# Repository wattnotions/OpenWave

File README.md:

# OpenWave
Open Source Ocean Wave Sensor

For latest updates on where this project is at, visit http://www.wattnotions.com/category/openwave/

Copyright 2019

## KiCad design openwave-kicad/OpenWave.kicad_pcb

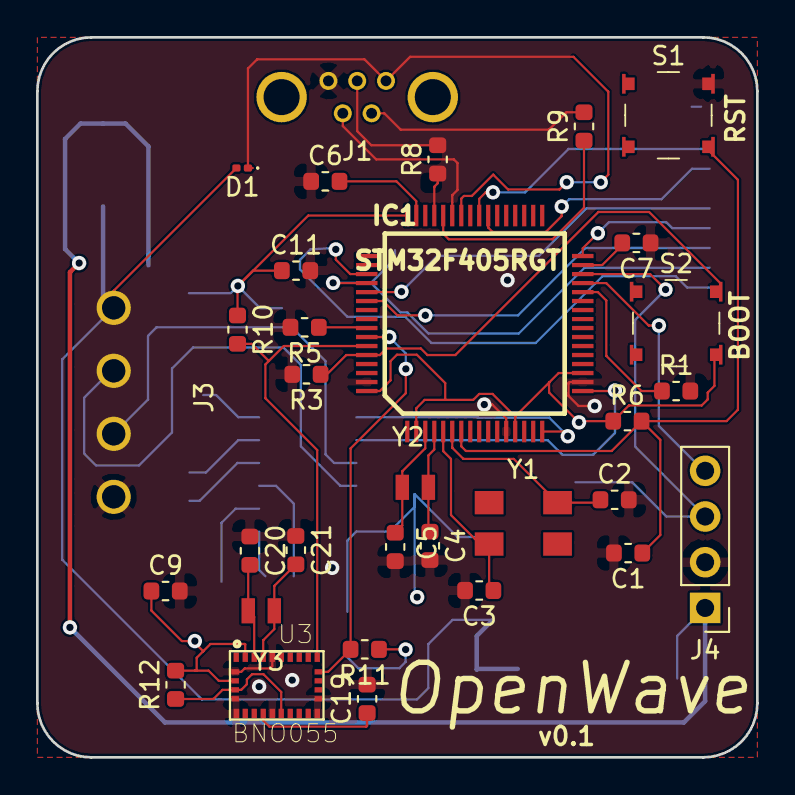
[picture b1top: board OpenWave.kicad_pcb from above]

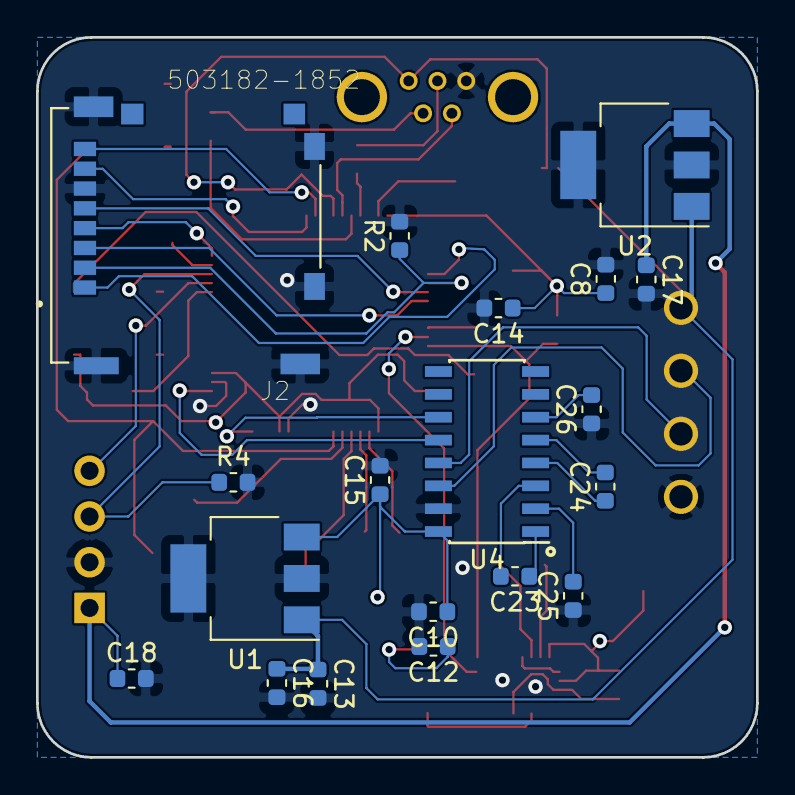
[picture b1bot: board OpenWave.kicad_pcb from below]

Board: 4 copper layers, 40.0 x 40.0 mm, 51 parts (19 on the bottom side), 44 nets.

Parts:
C1, C8, C9, C10, C11, C15, C18: 100n; C_0603_1608Metric
C2, C3, C4, C5: 12p; C_0603_1608Metric
C6, C7: 2u2; C_0603_1608Metric
C12: 4u7; C_0603_1608Metric
C13, C14, C16, C17: 1u; C_0603_1608Metric
C19: 22pf; C_0603_1608Metric
C20, C21: 12pf; C_0603_1608Metric
C23, C24, C25, C26: 0.1uF; C_0603_1608Metric
D1: D_Schottky; D_0201_0603Metric
IC1: STM32F405RGT; LQFP64
J1: USB_OTG; wurth_usb_connector
J2: 503182-1852; MOLEX_503182-1852
J3: Screw_Terminal_01x04; 4-WAY-PCB_SOCKET
J4: Conn_01x04_Female; PinHeader_1x04_P2.54mm_Vertical
R1: 1k; R_0603_1608Metric
R2: 10M; R_0603_1608Metric
R3, R4, R5: 100k; R_0603_1608Metric
R6: 10K; R_0603_1608Metric
R8, R9: 15R; R_0603_1608Metric
R10, R11, R12: 10k; R_0603_1608Metric
S1, S2: TL3315NF160Q; Switch_Tactile_SMD_4.5x4.5mm_TL3315NF160Q
U1: MIC5239-3.3YS; SOT-223-3_TabPin2
U2: MIC5209-4.2; SOT-223-3_TabPin2
U3: BNO055; LGA28R50P4X10_380X520X100
U4: MAX3232; SOIC-16_3.9x9.9mm_P1.27mm
Y1: 8MHz; QC5CA8_8mhz_oscillator
Y2: 32.768KHz; ABS06-32.768KHZ_smd_crystal
Y3: Crystal; ABS06-32.768KHZ_smd_crystal

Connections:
+3V3: C8.1, C9.1, C10.1, C11.1, C12.1, C14.1, C15.1, IC1.2, IC1.13, IC1.19, IC1.32, IC1.48, IC1.64, J2.4, R6.1, R10.1, R11.1, R12.2, S2.4, U1.3, U3.3, U3.28, U4.16
+5V: D1.1, IC1.42, J1.1
+12V: C13.1, C16.1, D1.2, J3.4, U1.1, U2.1
/4.2V: C17.1, C18.1, J4.1, U2.3
/BNO055/XIN32: C20.2, U3.27, Y3.1
/BNO055/XOUT32: C21.2, U3.26, Y3.2
/BOOT0: IC1.60, R3.1, S2.2
/FS_DM: IC1.44, R9.1
/FS_DP: IC1.45, R8.1
/FS_USB_ID: IC1.43, J1.4
/I2C1-SCK: IC1.58, R11.2, U3.19
/I2C1-SDA: IC1.59, R10.2, U3.20
/IO_PA2: IC1.16, U4.11
/IO_PA3: IC1.17, U4.12
/IO_PB2: IC1.28, R1.1
/IO_PB10: IC1.29, J4.4
/IO_PB11: IC1.30, J4.3, R4.1
/MMA_AVDD: IC1.57, R5.1
/N$1: C6.2, IC1.47
/N$2: C7.2, IC1.31
/N$5: C5.1, IC1.3, Y2.2
/N$6: C4.1, IC1.4, Y2.1
/N$9: C2.1, IC1.6, Y1.1
/N$10: C3.1, IC1.5, Y1.2
/NRST: C1.1, IC1.7, R6.2, S1.4
/RS232_RX: J3.2, U4.13
/RS232_TX: J3.3, U4.14
/SDIO_CK: IC1.53, J2.5
/SDIO_CMD: IC1.54, J2.3
/SDIO_D0: IC1.39, J2.7
/SDIO_D1: IC1.40, J2.8
/SDIO_D2: IC1.51, J2.1
/SDIO_D3: IC1.52, J2.2, R2.1
GND: C1.2, C2.2, C3.2, C4.2, C5.2, C6.1, C7.1, C8.2, C9.2, C10.2, C11.2, C12.2, C13.2, C14.2, C15.2, C16.2, C17.2, C18.2, C19.2, C20.1, C21.1, C25.1, C26.1, IC1.12, IC1.18, IC1.63, J1.5, J2.6, J2.P1, J2.P2, J2.P3, J2.P4, J2.P5, J3.1, J4.2, R1.2, R2.2, R3.2, R4.2, R5.2, S1.2, U1.2, U2.2, U3.2, U3.5, U3.6, U3.10, U3.15, U3.16, U3.25, U4.15
unnamed: C19.1, U3.9
unnamed: C23.1, U4.1
unnamed: C23.2, U4.3
unnamed: C24.1, U4.4
unnamed: C24.2, U4.5
unnamed: C25.2, U4.2
unnamed: C26.2, U4.6
unnamed: J1.2, R9.2
unnamed: J1.3, R8.2
unnamed: R12.1, U3.4, U3.11

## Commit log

2019-02-26 changed directory name of test data file
2019-02-26 added example dataset
2019-02-26 added list chunk function
2019-02-28 part way through chunk_integration
2019-02-28 chunk_integrate function first revision completed and working
2019-02-28 removed unneeded list copy
2019-02-28 added plot detrended velocity func
2019-02-28 added find_peaks and integrated into chunk_integrate
2019-02-28 added average max displacement calculation
2019-03-03 added example plot function
2019-03-03 cleaned up end debug related lines
2019-03-22 removed debug info - added example plot 2
2019-03-22 added zero crossing test to chunk integrate
2019-03-22 added comments to chunk_integrate()
2019-04-04 added remove dc offset, made chunk integrate better
2019-04-05 made chunk graph more accurate
2019-04-05 added sine wave test + triple subplot
2019-04-05 tidied up code, partioned into functions, removed debug code
2019-04-05 changed example csv file
2019-04-05 added time_to_get_chunky function
2019-04-05 renamed to openwave.py
2019-04-05 main script with fancy new name
2019-04-05 removed example plot functions
2019-04-06 moved to python-scripts directory
2019-04-06 new subfolder for python scripts
2019-04-06 added kicad project as subfolder
2019-04-06 cleaned up more debug code, left in working state
2019-04-06 added mic5239 datasheet
2019-04-06 added mic5239 v reg
2019-04-06 added bno055 lib and footprint
2019-04-06 added sheet for bno055
2019-04-06 added max3232 sheet
2019-04-06 added 4.2v reg datasheet
2019-04-06 added bluetooth header, 4.2v reg
2019-04-06 added max232 datasheet
2019-04-06 finished max232 schematic
2019-04-07 added bno055 datasheet
2019-04-07 finished bno055 schematic
2019-04-08 added sd card connector footprint
2019-04-08 added digikey lib
2019-04-08 added pyboard lib
2019-04-08 linked all footprints to symbols, ready for routing
2019-04-08 fixed unconnected nets, routing 15% done
2019-04-09 routing ...51 connections left
2019-04-09 routing finished
2019-04-09 replaced incorrect usb connector
2019-04-09 added openwave to front silk
2019-04-09 added pin 1 marker to max3232
2019-04-09 made screw terminal pads thicker
2019-04-09 made screw terminal pads even thicker
2019-04-10 working on zero crossing displacement calculations
2019-04-10 removed debug print from threshpeaks
2019-04-10 fixed chunk integrate bug caused by type
2019-04-10 added comments to time to get chunky
2019-04-10 removed old example data file
2019-04-10 updated to reflect new example data files
2019-04-10 new test data files
2019-04-10 added comments explaining functions
2019-04-11 increased zero crossing interval
2019-04-12 added peak detect and zero crossing displacement functions
2019-04-12 added percentage error calculatioN
2019-04-12 added make error measurements function
2019-04-12 added pretty table error output
2019-04-12 added arguments to script, error, zero and peak
2019-04-24 added lowpass bode plot, made zero and peak func smarter with plot=yes/no
2019-05-31 added readme
2019-11-25 moved test_data to root dir
2019-11-25 Created script1.m
2019-11-26 added .asv to gitignore
2019-11-26 add fft_example for matlab website
2019-11-26 got fft plot working with correct freq scale
2019-11-26 added imu displacement info doc
2019-11-28 got freq domain accel2disp example from stackoverflow
2019-12-09 added paper on bares wave sensor
2019-12-09 added paper on FFT-DDI method
2019-12-12 added oceanography book
2019-12-12 added data from ocean energy ireland
2019-12-12 moved arm data to seperate folder
2019-12-12 moved files to seperate folder
2019-12-13 added *.djvu to gitignore
2019-12-13 restructed related_docs folder
2019-12-13 modified dir structure
2019-12-16 added sine gen function
2019-12-16 gave more descriptive name
2019-12-17 added randraw lib for rayleigh gen
2019-12-17 added test plot script for rayleigh dist
2019-12-17 added stoptime argument
2019-12-17 started work on sig wave gen
2019-12-18 got vector append to array working
2019-12-18 added sample rate argument
2019-12-18 replaced hardcoded values with variables
2019-12-18 changed more hardcoded to variable
2019-12-18 add all waves together and plot done
2019-12-19 added formatted value printing
2019-12-19 renamed to oceanWaveSim
2019-12-19 made script into a function
2019-12-19 added fft plot function
2019-12-19 added comments
2019-12-19 fixed typo
2019-12-20 script to generate and plot sim waves
2019-12-20 added fs+stoptime to func args
2019-12-20 added local extema detection
2019-12-20 added ylines to plot
2019-12-20 commented out plot and debug prints
2019-12-20 got sig wave calc func working
2019-12-20 removed debug prints
2019-12-20 added value print
2019-12-20 removed debug code
2019-12-20 added % difference calc
2019-12-20 re-added sim wave plot +ylines
2019-12-20 re-organised m files
2019-12-20 added matlab readme
2019-12-21 added blog link to readme
2019-12-21 added plot labels and title
2019-12-23 added description of script
2019-12-23 removed whitespace
2019-12-23 renamed to sig_wave_ex1.m
2019-12-23 fixed if statement bug
2019-12-23 made sig_wave_ex2 script
2019-12-23 fixed sine calculation typo
2019-12-23 added debug print to sine gen loop
2019-12-23 added book
2019-12-23 added wave modelling library
2019-12-23 added academic paper
2019-12-26 added variance/area comparison
2019-12-26 example psd func that returns area
2019-12-27 updated matlab files readme
2019-12-28 added sig wave height calc
2019-12-28 added accel2disp function
2019-12-28 added disp2Accel function
2019-12-28 added poorly named disp_to_accel script
2019-12-28 added dc offset removal
2019-12-28 added paper on accel integration
2019-12-28 added high pass filter
2020-01-02 added script to test rotating arm data
2020-01-02 changed fig number
2020-01-02 tidied up script and added comments
2020-01-02 added formatTimestamp func
2020-01-02 added detrend
2020-01-02 changed script to use time from csv file
2020-01-02 script to test the timestampFormat func
2020-01-02 started rayleigh sim wave gen
2020-01-02 changed float to print only 2 decimal places
2020-01-02 changed wave gen to fit rayleigh dist
2020-01-02 variable name change
2020-01-02 added axis labels on disp plot
2020-01-02 removed detrend - not needed
2020-01-02 added semicolon to suppress output
2020-01-02 changed highpass cutoff to 0,1Hz
2020-01-06 commented out plot code
2020-01-06 renamed to psdArea.m
2020-01-06 changed to histcounts to stop hist plot
2020-01-06 moved to main folder
2020-01-06 added std dev hight print
2020-01-06 moved
2020-01-06 changed to use histcounts instead of histogram
2020-01-06 updated to use psdArea
2020-01-06 added description of func
2020-01-06 added function descriptions
2020-01-06 updated description
2020-01-06 fixed integer indexing warning
2020-01-06 updated to new accel2Disp
2020-01-06 added script description
2020-01-07 changed folder structure
2020-01-07 renamed file
2020-01-07 added average wave height output
2020-01-07 added comment
2020-01-07 commented plotting in accel2disp
2020-01-08 added velocity output
2020-01-08 added comments to plot section
2020-01-08 added wave sensor info docs
2020-01-08 added wave sensor docs
2020-01-08 renamed folder
2020-03-12 added linear rail arduino program
2020-07-11 added bn055 lib
2020-08-14 basic working example
2020-08-14 datasheets added
2020-08-14 dir cleanup
2020-08-17 bluetooth serial working
2020-08-21 added calib data read to file
2020-08-21 added print calibration function
2020-08-21 got read and save calib data working
2020-08-21 added calibration data save and load functions
2020-08-21 fixed issues with calibration functions
2020-08-21 replaced calib code with new lib function
2020-08-21 started work on adding timer
2020-08-22 basic version of i2c linaccel timer read working
2020-08-22 progress on i2c read uart send with timer
2020-08-22 changed interrupt to just set flag - in prog
2020-08-22 reading i2c data and timetamp from within isr working
2020-08-22 isr read working, tight timing looks good, sub micro second
2020-08-23 bluetooth send with i2c data + timestamp working
2020-08-23 added extra comments
2020-08-24 improved serial data formatting
2020-08-24 basic bt serial read working
2020-08-29 fixed timer starting before i2c init issue
2020-09-02 added auto calibrate function
2020-09-02 added save to csv file
2020-09-02 fixed calib file bug
2020-09-02 loading calib data from file working reliably now
2021-02-08 added end stop switch test read
2021-02-09 added step to mm test code
2021-02-11 added script for sending sim data to arduino
2021-02-11 various linear rail related stuff
2021-02-12 started serial comms
2023-05-20 added esp32-s2 feather wing code - basic func working
2023-05-24 moved stuff to old folder
2023-05-24 got basic sending accel ovver wifi going
2023-05-25 tidied up sample code
2023-05-25 added openwave lib changed code.py to use it
2023-05-25 got wifi accel streaming with openwave lib
2023-05-25 got file writing working - added openwave linaccel record func
2023-05-28 added rtc ntp wifi update method
2023-11-22 added linear rail related sw
